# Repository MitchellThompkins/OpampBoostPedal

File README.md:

## Description

This is a low-cost op-amp boost pedal meant for use with guitar. The form factor is intended to be very small. Included you will find the eagle files for the board, wiring diagrams, finished photos, pspice simulation files, and a bill of materials to estimate the total cost. PSpice simulations are also included.

### Current revision of the PCB:

### The populated board:

### Finished Pedal:

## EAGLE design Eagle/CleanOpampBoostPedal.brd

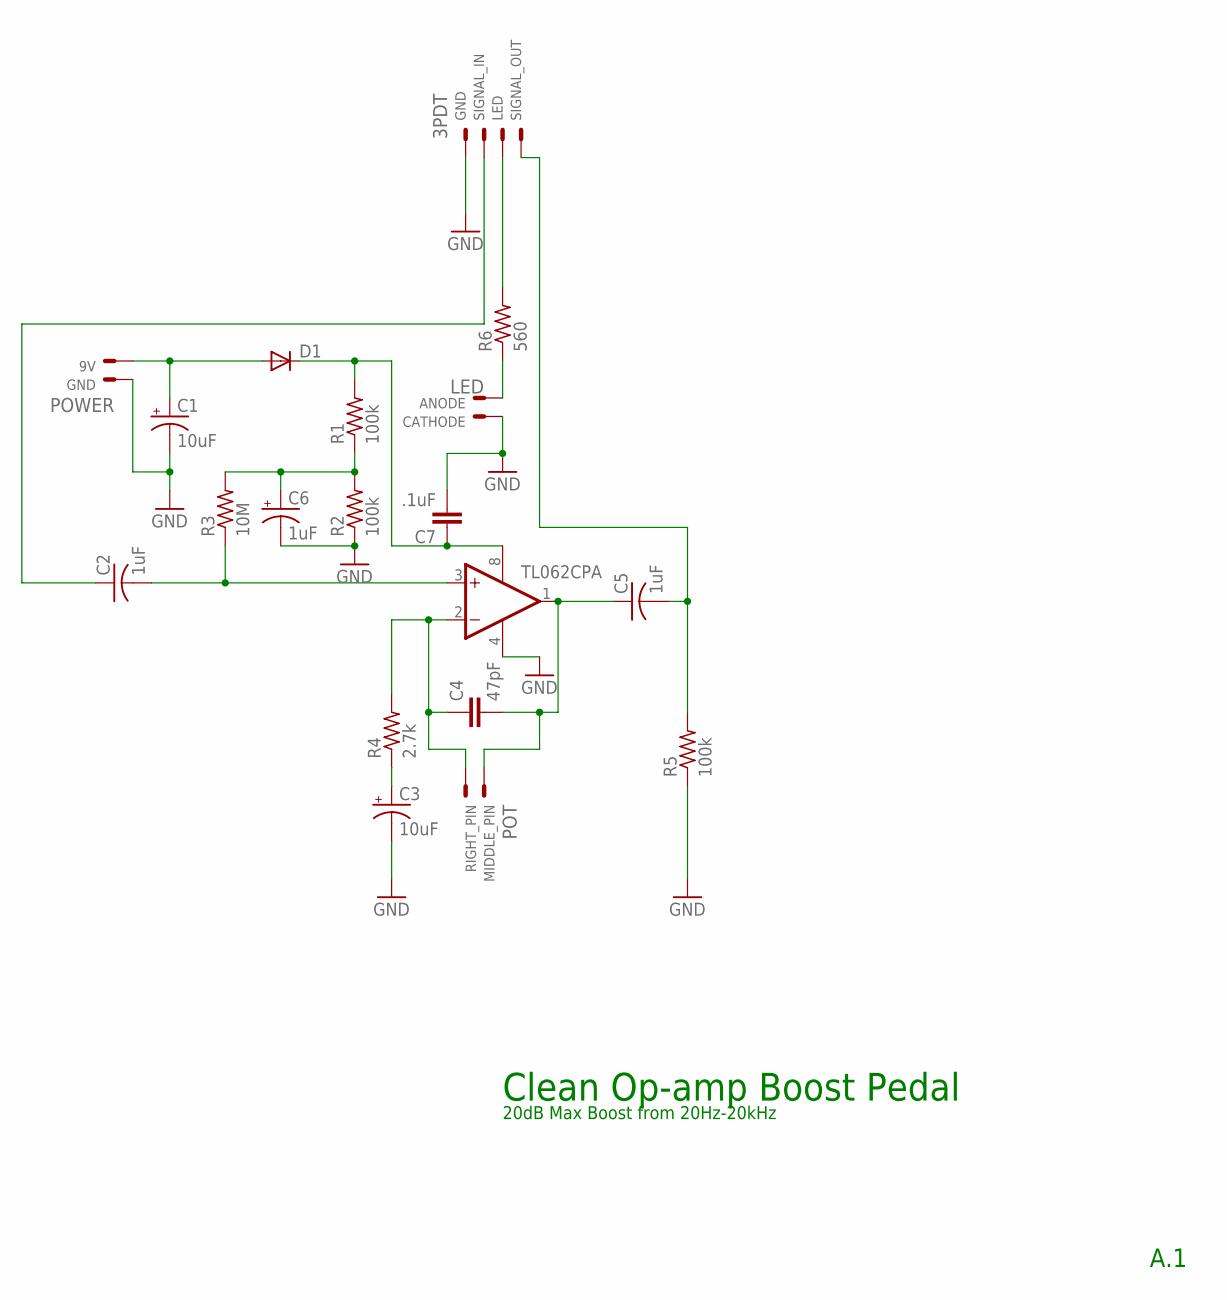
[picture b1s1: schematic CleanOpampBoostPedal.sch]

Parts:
3PDT: 22-23-2041
C1, C3: 10uF; E2,5-6E
C2, C5: 1uF; C050-045X075
C4: 47pF; C2.5-2
C6: 1uF; E2,5-6
C7: .1uF; C2.5-2
D1: DIODE-D-2.5; D-2.5
LED: 22-23-2021
POT: 22-23-2021
POWER: 22-23-2021
R1, R2, R5: 100k; 0207/2V
R3: 10M; 0207/2V
R4: 2.7k; 0207/2V
R6: 560; 0207/2V
TL062CP: LM1458N; DIL08

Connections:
GND: 3PDT.1, C1.-, C3.-, C6.-, C7.2, LED.1, POWER.1, R2.1, R5.1, TL062CP.4 (V-)
unnamed: C2.2, R3.1, TL062CP.3 (+IN)
unnamed: 3PDT.3, R6.2
unnamed: C7.1, D1.C, R1.2, TL062CP.8 (V+)
unnamed: C1.+, D1.A, POWER.2
unnamed: LED.2, R6.1
unnamed: C3.+, R4.1
unnamed: C4.1, POT.2, R4.2, TL062CP.2 (-IN)
unnamed: C4.2, C5.1, POT.1, TL062CP.1 (OUT)
unnamed: 3PDT.4, C5.2, R5.2
unnamed: 3PDT.2, C2.1
unnamed: C6.+, R1.1, R2.2, R3.2

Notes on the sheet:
20dB Max Boost from 20Hz-20kHz
Clean Op-amp Boost Pedal
A.1

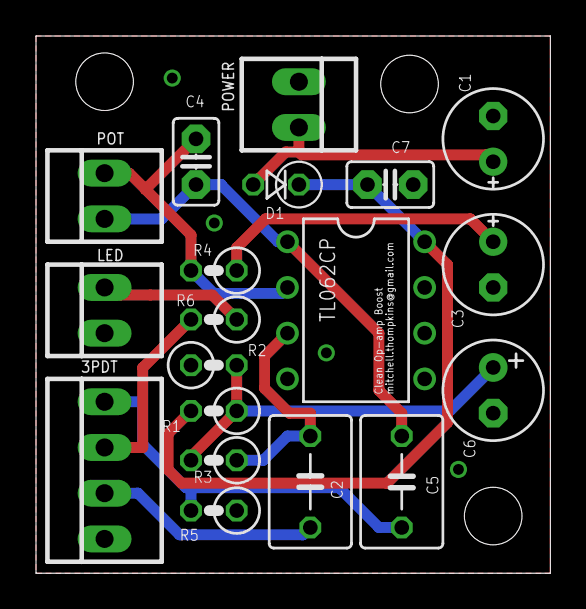
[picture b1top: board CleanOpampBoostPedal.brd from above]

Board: 2 copper layers, 28.6 x 29.8 mm, 19 parts (0 on the bottom side), 12 nets.

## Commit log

2015-11-01 Added Readme. Removed OS files.
2015-11-01 Added Readme. Fixed OS files.
2016-04-04 Modified Readme

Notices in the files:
parts and their libraries:
SparkFun: Licensing: CC v3.0 Share-Alike You are welcome to use this library for commercial purposes.
